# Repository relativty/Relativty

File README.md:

Dale una mirada a esta guía en [Español](README.es.md)
<h1 align="center">
	
</h1>

<h3 align="center">
	Open-source VR headset with SteamVR support.
</h3>
<p align="center">
	<strong>
		<a href="https://relativty.com">Website</a>
		•
		<a href="https://discord.gg/jARCsVb">Discord</a>
	</strong>
</p>

I’m <a href="https://twitter.com/maxim_xyz?lang=en">Maxim xyz</a> and when my best friend Gabriel Combe and I were 15 years old we built our own VR headset because we couldn't afford to buy one.

5 years later : this headset became Relativty.

* Fully Open-source - **hardware**, **software**, **firmware**.
* **Steam VR** support.
* Natively displays **2K** resolution at **120FPS**.
* Compatible with **Arduino**.
* Experimental **Body-Tracking**

**This repo serves as a Build guide, to learn more about the headset see you at <a href="https://relativty.com">Relativty.com</a>**

Made for Hackers
-
Relativty is **NOT A CONSUMER PRODUCT**. We made Relativty in my bedroom with a soldering iron and a 3D printer and we expect you to do the same: **build it yourself**.

Relativty at its basics is a 3 Degrees of Freedom (3-DoF) VR headset with no built-in controller support, designed to work with SteamVR.
This may limit its practical usability for games that demand knuckle-style VR controllers.
If you are looking for a more full-featured DIY VR project 6-Dof tracking and controller support, we recommend you check out <a href="https://github.com/HadesVR/HadesVR">HadesVR</a>.

Whether or not you are building either Relativty or HadesVR, or if you just want to join our community and hang out, we invite you to <a href="https://discord.gg/F8GNKjy6RF">Relativty's Guild on Discord</a>.

It is a place for the DIY/Open-Source VR community to learn, grow, share knowledge, and ask for help. 

# Start Building Relativty

# Building The Hardware
## 1. CURRENT RECOMMENDED BUILD - As of May 2023
### 1.1 Introduction
This is an updated build guide to help people who recently discovered Relativty. It aims to explain how to build the minimum functional product, which can be further improved upon and modified to the individual's liking. The original build guide can still be found further below.

            Following this guide to build a Relativty headset assumes basic understanding of electronics and programming Arduino boards.
            A VR headset is a complex system and can be difficult to figure out what is not working if you get stuck with the build.
            If you encounter any issues, join our Discord and ask for help, we are happy to assist.

### 1.2 ELECTRONICS

The following electronic components are required:

- ATmega32U4 Microcontroller (MCU) with USB HID support, such as an <a href="https://www.amazon.co.uk/diymore-Atmega32U4-Development-Microcontroller-Header/dp/B0BKGSVX2X">Arduino Pro Micro</a>
- Inertial Measurement Unit (IMU) that is supported by the <a href="https://github.com/LiquidCGS/FastIMU">FastIMU Library</a>
- A small, high resolution and high refresh rate PC display + driver board. <a href="https://github.com/HadesVR/HadesVR/blob/main/docs/Headset.md#displays">This segment of the HadesVR documentation presents possible good options you can choose from</a>. It is important to note that these displays connect to a DRIVER BOARD, which then connects to your computer. ALWAYS purchase the driver board and display(s) in the same bundle if you can to ensure they are compatible with each other. If you have further questions about displays, join us at <a href="https://discord.gg/F8GNKjy6RF">Relativty's Guild on Discord</a>.
```
NOTES on VR DISPLAYS:
- The display does not connect to the Microcontroller, it only connects to the Computer running your VR Apps.
- Technically, any PC display/monitor can be configured as the display used by Relativty. Therefore, you can simply test your build on your PC monitor
first to make sure it works, before you decide to spend a significant amount of money on lenses, display(s) and other parts.
- High performance, small form factor displays are expensive, and often very delicate. Handle them with care! :)
```

### 1.2.1 Wiring the IMU and MCU
The IMU needs to be connected to the MCU for power and communication.
The MCU connects to your computer via USB to send the IMU readings to SteamVR.

In case of an Arduino Pro Micro, you need to connect the following pins:
```
Pro Micro       IMU
VCC         ->  VCC  
GND         ->  GND  
SDA(pin 2)  ->  SDA  
SCL(pin 3)  ->  SCL  
```  
If you use a different MCU, the SDA and SCL pins might be mapped to different pin numbers.

Also, make sure that the VCC of your MCU is compatible with the rated operating voltage of your IMU.

Supplying incorrect voltage to electronic components may cause damage to them.

The MCU itself simply connects to your computer via the USB port.

### 1.2.2 Connecting the display
As mentioned previously, any display that is compatible with a personal computer should be able to function as your VR display.

In case you are using the recommended one or a similar component that is powered via micro-USB or other USB standard, it is possible that you will encounter situations where the board does not power up. This could be either because the micro-USB cable you are using is too long (so the board cannot power up because the voltage dropped too much), or the board is unable to turn on because the USB port it connects to on the computer side is simply unable to supply enough power. In this case, you might need to try different ports on your computer or a powered USB hub.

### 1.3 MECHANICAL BUILD

The following parts are required for the Mechanical Build:

- Housing - .STL files for 3D-printable model provided in Relativty_Mechanical_build folder.
- Lenses -  for building the 3D-printable headset, Lenses with 40mm diameter/50mm focal length required. You can often find these on Aliexpress or similar.
- Strap and Facial Interface - e.g. replacement strap + foam for HTC Vive. You can often find these on Aliexpress or similar.

If you do not have access to 3D-printing, it is also possible (and MUCH simpler) to just use an Android VR Phone case, and modify it to fit your screen and so that you can attach your IMU and MCU to it.

The advantage of this approach is that you get everything in one package, often including IPD adjustment.

### 1.4 SOFTWARE SETUP

### 1.4.1 Introduction

Relativty depends on 2 main software components:
- the Arduino firmware
- the SteamVR driver

As the system is designed to work with SteamVR, you need to have Steam installed and SteamVR downloaded on your computer.

### 1.4.2 Programming your MCU

As previously mentioned, we recommend you use an Arduino Pro Micro and an IMU supported by the FastIMU Library.
FastIMU is an awesome package that supports many commonly used IMUs and comes with a pre-written Arduino sketch that works with Relativty.

First, you will need to install the Arduino IDE and connect your MCU to your computer via the USB connector.

Once you have it connected and verified your Arduino IDE can work with your MCU, download FastIMU from the library manager.

Wire up your IMU as recommended in Section 1.2.1.

Find the Examples/Fastimu/Calibrated_relativty sketch in your Arduino IDE:

And finally, Upload it to your MCU.

FastIMU also includes a built-in calibration tool that can store the calibration data on the IMUs EEPROM.

Calibrating the IMU may help with sensor drift that you can experience over time while using Relativty.

After uploading Calibrated_relativty sketch to the IMU, you can open the Arduino Serial Monitor to initiate a calibration sequence:

      NOTE: you only have to do this once, but make sure to follow the instructions given to you in the serial monitor.

### 1.4.3 Installing The SteamVR Driver

To install the Relativty SteamVR driver:
- download the <a href="https://github.com/relativty/Relativty/archive/refs/heads/master.zip">master repository</a>
- inside Relativty-master find the Relativty_Driver\Relativty folder and copy it to your SteamVR installation's drivers directory.

### 1.4.4 Configuring The SteamVR Driver

Once you copied the driver files, it is time to configure the driver to work with your setup and computer.

Inside drivers\Relativty\resources\settings, there should be a file called default.vrsettings.

This is the configuration file for the driver.

There are a few things that you need to change.

### Configuring the driver to talk to the MCU
ASSUMING you use an Arduino Pro Micro and the FastIMU library:

In the Relativty_hmd segment find these values:
- hmdPid
- hmdVid
- hmdIMUdmpPackets

and change the values like so:

```
      "hmdPid" : 32823,
      "hmdVid": 9025,
      "hmdIMUdmpPackets":  false,
```

If you are using a different MCU, you need to figure out the USB PID and VID values.

Easiest way is to connect it to your computer via USB and check in Arduino IDE.

In the menu bar, select Tools/Get Board Info:

Take the PID and VID values and convert them to decimal with a <a href="https://www.rapidtables.com/convert/number/hex-to-decimal.html">hex converter</a>.

The converted values then go into the hmdPid and hmdVid values in default.vrsettings.

### Configuring the Display Settings
Now let's look at configuring the driver to work with your Display.

The config variables for the display are in the Relativty_extendedDisplay segment:

For the VR Viewport window's point of origin:
```
      "windowX" : 3440,
      "windowY" : 0,
```

For the VR Viewport's actual size
```
      "windowWidth" : 1920,
      "windowHeight" : 1080,
```

For the VR Viewport's rendering resolution - this should be normally the same as the size
```
      "renderWidth" : 1920,
      "renderHeight" : 1080,
```

And some miscellaneous settings:
```
      "DistortionK1" : 0.4,
      "DistortionK2" : 0.5,
      "ZoomWidth" : 1,
      "ZoomHeight" : 1,
      "EyeGapOffsetPx" : 0,
      "IsDisplayRealDisplay" : true,
      "IsDisplayOnDesktop" : true
```
If the point of origin and size is not configured correctly, the driver will crash and SteamVR will not display anything!

Therefore we need to have a look at and understand the coordinate system SteamVR uses for displays.

Windows always assumes one of the connected displays as your Primary Display.

You can verify which one is your Primary in Display Settings.

You can select each of your displays with the mouse. The one that has "Make this my main display" checkbox greyed out is your Primary Display.

THIS GUIDE ASSUMES THAT THE TOP EDGE OF ALL OF YOUR DISPLAYS ARE ALIGNED IN WINDOWS DISPLAY SETTINGS (as seen on the screenshots)

Consequently, checking the same on another, non-primary display will make that one your Primary.

The TOP LEFT corner of your Primary Display is the ORIGIN POINT of SteamVR's display coordinate system.

To be able to tell SteamVR where to draw the VR Viewport on your displays, you need to make sure you understand this fact and as a result can identify the correct point of origin for the Viewport.

For example, in a setup like this:

Because the "1" screen is the primary, and the "3" screen is the VR Display, the origin point (the 0,0 coordinate) is on the top left of the "1" screen.

This screen has 3440x1440 resolution.

This means it occupies the X axis from 0 to 3439, and the next screen on its right starts at point 3440.

Therefore, in this case the correct windowX and windowY values are:

```
      "windowX" : 3440,
      "windowY" : 0,
```

If "2" screen was the VR display (and "1" is still the Primary), the correct values would be:

```
      "windowX" : -1920,
      "windowY" : 0,
```
Because the "2" screen's coordinates occupy space over the other side of the origin point.

For windowWidth,windowHeight,renderWidth,renderHeight, simply set the Native Resolution of your VR display.

Once this is all set, save the settings file.

Now you should be ready to start SteamVR.

If everything is set up right, you should get straight into the vr holodeck area:

If you are encountering any issues with your build:
- open the SteamVR Web Console and copy the entire log file
- Join <a href="https://discord.gg/F8GNKjy6RF">Relativty's Guild on Discord</a>, tell us about the issues you are facing, and upload the log file in the chat. 

### IF YOUR VR WINDOW DISAPPEARS AFTER CLICKING ON IT:

Open Windows PowerShell and paste these commands into the command line, then hit enter:

```
get-process vrcompositor | stop-process -Force;cd "C:\Program Files (x86)\Steam\steamapps\common\SteamVR\bin\win64";.\vrcompositor.exe
```

Afterwards the VRCompositor should remain stable, so you only have to do this once per session.

# 2. LEGACY BUILD
The hardware is based on the Relativty Motherboard which includes an Atmel SAM3X8E ARM Cortex-M3 processor and uses an MPU-6050 as it’s IMU.
Alternatively, any processor that supports the ArduinoCore and is connected to an MPU-6050/MPU-9250 can be used as the hardware for Relativty. Both methods are explained below.

## Building The Relativty Motherboard
### PCB Manufacturing.

We first start with the naked PCB.

it can be manufactured and bought for around $4 on websites like <a href="https://jlcpcb.com/">jlcpcb</a>.

You’ll need to provide the Gerber file folder `Relativty_Electronics_build/GerberFiles.zip` which describes the shape of the board.

### Assembling

Soldering the components onto the naked PCB. 

You’ll have to buy the components listed in one of the two BOMs, depending on availability:
- `Relativty_Electronics_build/Assembly/jlcpcb.com_motherboard_BOM.csv` 
- `Relativty_Electronics_build/Assembly/motherboard_BOM.xlsx`

Where to position those components on the PCB is described in the file `Relativty_Electronics_source/motherboard.brd` which can be opened in Eagle.

#### Using an Arduino

An alternative to the Relativty Motherboard is to use an Arduino Due and to connect it to an MPU-6050.
```
5V      -> VCC  
GND     -> GND  
SDA(20) -> SDA  
SCL(21) -> SCL  
PIN 2   -> INT  
```

If you are using an MPU-9250 with the alternative firmware provided the pinout is:

```
5V      -> VCC  
GND     -> GND  
SDA(20) -> SDA  
SCL(21) -> SCL   
```

Then push the `ERASE` and the `RESET` button on the Arduino Due and you’ll be able to install the Relativty Firmware.

#### Installing The Relativty Firmware

You’ll now need to install the Relativty board in the Arduino IDE. 

To do that copy that JSON URL: https://raw.githubusercontent.com/relativty/Relativty/master/Relativty_Firmware/package_Relativty_board_index.json and open the Arduino IDE

In Arduino, Click File and then Preferences:

- If you are using the Relativty PCB, aad the JSON URL to the `Additional Boards Manager` text box.
- Go to `Tools > Board > Board Manager` and you should see the Relativty Board, click install.
- Reboot the Arduino IDE and under Tools > Boards, select Relativty.
- You can now open `Relativty_Firmware/firmware/firmware.ino` and upload it to your board.

If you are using a different board e.g. Arduino Due:

- install contents of `Relativty_Firmware\Relativty_board\` to your Arduino IDE
- if you are using MPU-6050, use `Relativty_Firmware/firmware/firmware.ino`
- if you are using MPU-9250, use `Relativty_Firmware\MP9250-HID\MP9250-HID\MP9250-HID.ino`

# Building The Mechanical Parts

## Assembling the HMD

All the files needed for the 3D printing can be found in the `Relativty_Mechanical_build` folder and the screws needed to assemble the Headset are listed in `screws_BOM.xlsx`.

We've used parts from Aliexpress:

- <a href="https://www.aliexpress.com/item/33058848848.html">The Strap</a>, 
- <a href="https://www.aliexpress.com/item/4000199486058.html">The Foam</a>,
- <a href="https://www.aliexpress.com/item/33029909783.html">The Lenses</a> (40mm diameter/50mm focal length).

### The screen for the HMD

Relativty Headset runs a dual-screen at 120FPS 2K, however, because of the open nature of Relativty you can equip it with any screen.

Our model can be found on Aliexpress, but depending on the vendor similar screens can cost from $150 to $190. You'll have to hunt and maybe wait for the right vendor at the right price to get the display for cheap (or buy in bulk). 

This is [the model we used](https://www.aliexpress.com/item/32975198897.html).

### Setting Up the Software

#### Installing Relativty Driver for SteamVR

The Relativty Driver is contained within `Relativty_Driver/Relativty` folder. 

⚠️ You’ll need to set it up by editing the JSON file `Relativty_Driver/Relativty/resources/settings/default.vrsettings`

If you are not using a Relativty PCB, you will need to change these:

      "hmdPid" : 9,
      "hmdVid": 4617,
	  
These are the USB HID device's unique Vendor and Producit Identifieres (pid/vid)

If you are using and Arduino Due, the correct values will be:

      "hmdPid" : 62,
      "hmdVid" : 9025,
	  
In case you are using a different board, the process to get the right values is as below:

1.	Plug your board in

2.	Select your board in Arduino IDE and click Tools/Get Board info. you will see something like this:

```
	BN: Arduino Due (Native USB Port)
	VID: 2341
	PID: 003e
	SN: HIDHB
```
3.	Make note of the VID and PID numbers. These are hexadecimal values.

	To apply them to the config, they need to be converted to int.
	
	If you are unsure how to do that, there is plenty online converters available.
	
	Such as: https://www.rapidtables.com/convert/number/hex-to-decimal.html

4.	Change your hmdPid and hmdVid values to the converted values.

Next, you need to set up the display coordinates and resolution.

At first, you should have the HMD's display set up as a secondary screen extending your desktop,

aligned onto the top right corner of your primary display.

In the config file's "Relativty_extendedDisplay" segment, find and set these:
```
      "windowX" : *whatever your primary screen resolution's width is*,
      "windowY" : 0,
      "windowWidth" : *HMD's native resolution width*,
      "windowHeight" : *HMD's native resolution height*,
      "renderWidth" : *HMD's native resolution width*,
      "renderHeight" : *HMD's native resolution height*,
	  
	  And at the bottom of this segment:
	  
      "IsDisplayRealDisplay" : true,
      "IsDisplayOnDesktop" : true
```  
	  
Make sure not to delete any "," symbols as that will break the config.

Only the last item in the config should not have a "," symbol.

If for whatever reason the above settings do not work out for you try:

Set your HMD display as a mirrored display of your primary display.

Change config as follows:
```
      "windowX" : 0,
      "windowY" : 0,
      "windowWidth" : *HMD's native resolution width*,
      "windowHeight" : *HMD's native resolution height*,
      "renderWidth" : *HMD's native resolution width*,
      "renderHeight" : *HMD's native resolution height*,
	
      "IsDisplayRealDisplay" : false,
      "IsDisplayOnDesktop" : true
	
```	
⚠️ Please note that this may result in keyboard/mouse input not being captured by the VR window, should your game require it, it might become unplayable.

You can also make IPD (Interpupillary Disance) adjustments within the configuration file:

In the "Relativty_hmd" segment find and adjust:

```
      "IPDmeters" : 0.063,
```

You can also change the lens distortion correction by changing these:

```
      "DistortionK1" : 0.4,
      "DistortionK2" : 0.5,
```

You can now install Relativty Driver:
- Locate your `vrpathreg.exe` program, usually located at `C:/Steam/steamapps/common/SteamVR/bin/win64/vrpathreg.exe`
- Then open the Windows Command Prompt and run the following commands:
`cd C:/Steam/steamapps/common/SteamVR/bin/win64
vrpathreg.exe`

And then assuming your `Relativty_Driver/Relativty` driver folder is located at:
`C:/code/Relativty_Driver/Relativty`
- run `vrpathreg adddriver C:/code/Relativty_Driver/Relativty`

Relativty Driver is now installed. You can uninstall it any time by running:  
- `vrpathreg removedriver C:/code/Relativty_Driver/Relativty`

#### Setting up the Experimental 3D Tracking

The tracking is still very experimental and can only be run on NVIDIA GPU due to the usage of CUDA. The tracking makes uses of only a video input and an Artificial Neural Network AI trained to estimate a 3D body position. 

This method is nothing close to the precision or freedom of movements of a dedicated sensor however we believe that the model can be trained and improved by orders of magnitude.

You first need to connect a webcam to your computer and install Python 3.8.4 and select the option to add it to the path. Then install `PyTorch`, you can do so by running the following commands:

`python -m pip install torch===1.6.0 torchvision===0.7.0 -f https://download.pytorch.org/whl/torch_stable.html`

Then proceed to install `CUDA Toolkit 11.0.`

You’ll then need to download the Folder `PYTHONPATH` at https://github.com/relativty/Relativty/releases and add its location to `PyPath` in the `JSON Relativty_Driver/Relativty/resources/settings/default.vrsettings`

Set `tracking` to 1. The tracking is now turned on and can be turned off anytime by setting `tracking` to 0. The tracking can also be calibrated depending on your camera, this can be done by tweeking `scalesCoordinateMeter` and `offsetCoordinate`. `scalesCoordinateMeter` correspond to the delta of coordinates in a given axis calculated by the AI after normalization when you move 1 meter in that given axis.

**Note:** If you plan on using mpu9250 firmware do not forget to switch to it in the driver by setting `hmdIMUdmpPackets` to `false`:
`"hmdIMUdmpPackets":  false,`

## Final Steps

Everything is now set up to start playing. 

To start using Relativty:
- Lay the headset on a flat surface with the front panel facing the ground
- Plug in the Headset.
It’ll automatically calibrate after a few seconds.

You can now run any SteamVR game!

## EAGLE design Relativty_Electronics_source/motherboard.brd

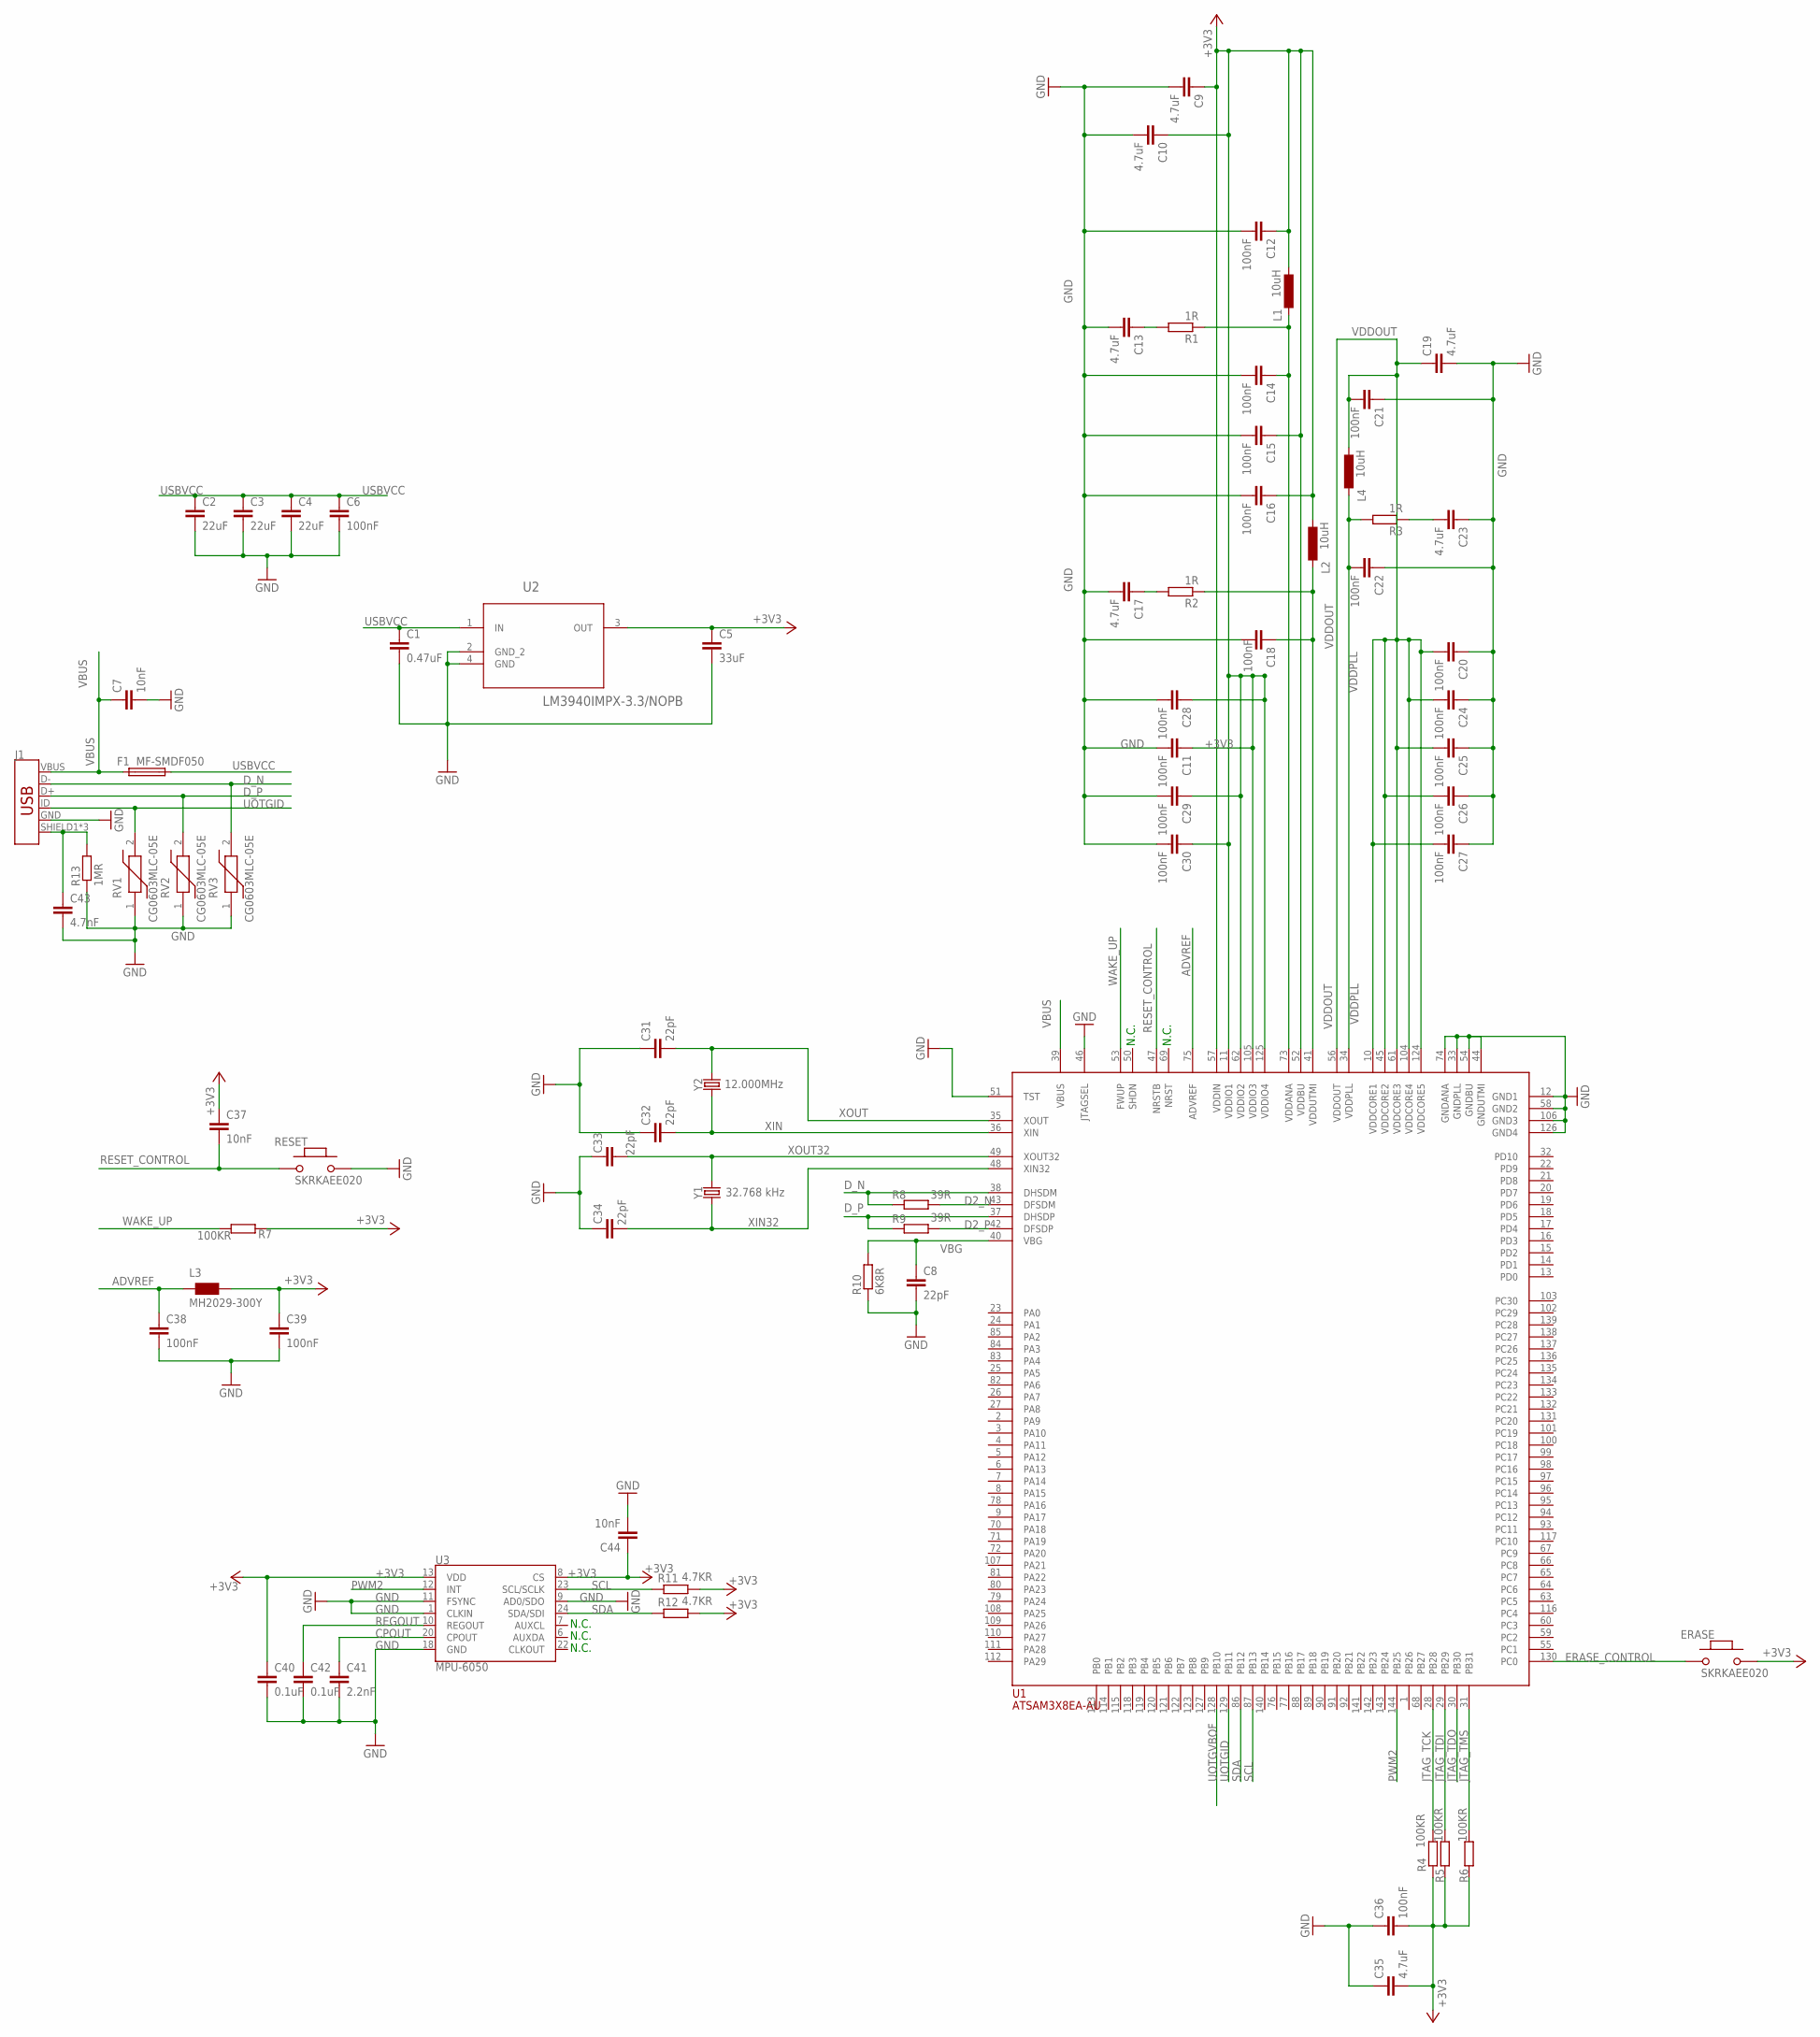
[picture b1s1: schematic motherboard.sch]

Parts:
C1: 0.47uF; C0805
C2, C3, C4: 22uF; C1206
C5: 33uF; C1206
C6, C11, C12, C14, C15, C16, C20, C21, C22, C24, C25, C26, C27, C28, C29, C30, C36, C38, C39: 100nF; C0402
C7, C37, C44: 10nF; C0402
C8, C31, C32, C33, C34: 22pF; C0402
C9, C10, C13, C17, C19, C23, C35: 4.7uF; C0805
C18: 100nF; C0201
C40, C42: 0.1uF; C0402
C41: 2.2nF; C0402
C43: 4.7nF; C0402
ERASE: SKRKAEE020; SOD4829X200
F1: MF-SMDF050
J1: USB_MICRO-B_FEMALE-SMT; USB-B-MICRO-SMD
L1, L2, L4: 10uH; L2012C
L3: MH2029-300Y; 2012-EU
R1, R2, R3: 1R; R0402
R4, R5, R6, R7: 100KR; R0603
R8, R9: 39R; R0402
R10: 6K8R; R2012
R11, R12: 4.7KR; R0805
R13: 1MR; R1206
RESET: SKRKAEE020; SOD4829X200
RV1, RV2, RV3: CG0603MLC-05E; VARC1608X55N
U1: ATSAM3X8EA-AU; LQFP144
U2: LM3940IMPX-3.3/NOPB; SOT230P696X180-4N
U3: MPU-6050; QFN-24-EP
Y1: 32.768 kHz; CRYSTAL-SMD-3.2X1.5MM
Y2: 12.000MHz; CRYSTAL-SMD-3.2X2.5MM

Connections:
+3V3: C5.1, C9.1, C10.1, C11.1, C12.1, C15.1, C16.1, C28.1, C29.1, C30.1, C35.2, C36.2, C37.1, C39.1, C40.1, C44.1, ERASE.2, L1.1, L2.1, L3.2, R4.1, R5.1, R6.1, R7.1, R11.2, R12.2, U1.11 (VDDIO1), U1.52 (VDDBU), U1.57 (VDDIN), U1.62 (VDDIO2), U1.105 (VDDIO3), U1.125 (VDDIO4), U2.3 (OUT), U3.8 (CS), U3.13 (VDD)
ADVREF: C38.1, L3.1, U1.75 (ADVREF)
CPOUT: C41.1, U3.20 (CPOUT)
D2_N: R8.2, U1.43 (DFSDM)
D2_P: R9.2, U1.42 (DFSDP)
D_N: J1.D-, R8.1, RV3.2, U1.38 (DHSDM)
D_P: J1.D+, R9.1, RV2.2, U1.37 (DHSDP)
ERASE_CONTROL: ERASE.1, U1.130 (PC0)
GND: C1.2, C2.2, C3.2, C4.2, C5.2, C6.2, C7.2, C8.2, C9.2, C10.2, C11.2, C12.2, C13.2, C14.2, C15.2, C16.2, C17.2, C18.2, C19.2, C20.1, C21.1, C22.1, C23.1, C24.1, C25.1, C26.1, C27.1, C28.2, C29.2, C30.2, C31.1, C32.1, C33.1, C34.1, C35.1, C36.1, C38.2, C39.2, C40.2, C41.2, C42.2, C43.2, C44.2, J1.GND, R10.1, R13.1, RESET.2, RV1.1, RV2.1, RV3.1, U1.12 (GND1), U1.33 (GNDPLL), U1.44 (GNDUTMI), U1.46 (JTAGSEL), U1.51 (TST), U1.54 (GNDBU), U1.58 (GND2), U1.74 (GNDANA), U1.106 (GND3), U1.126 (GND4), U2.2 (GND_2), U2.4 (GND), U3.1 (CLKIN), U3.9 (AD0/SDO), U3.11 (FSYNC), U3.18 (GND)
JTAG_TCK: R4.2, U1.28 (PB28)
JTAG_TDI: R5.2, U1.29 (PB29)
JTAG_TDO: U1.30 (PB30)
JTAG_TMS: R6.2, U1.31 (PB31)
unnamed: C43.1, J1.SHIELD1 (SHIELD), J1.SHIELD2 (SHIELD), J1.SHIELD3 (SHIELD), R13.2
unnamed: C13.1, R1.2
unnamed: C17.1, R2.2
unnamed: C23.2, R3.1
unnamed: C14.1, L1.2, R1.1, U1.73 (VDDANA)
unnamed: C18.1, L2.2, R2.1, U1.41 (VDDUTMI)
PWM2: U1.144 (PB25), U3.12 (INT)
REGOUT: C42.1, U3.10 (REGOUT)
RESET_CONTROL: C37.2, RESET.1, U1.47 (NRSTB)
SCL: R11.1, U1.87 (PB13), U3.23 (SCL/SCLK)
SDA: R12.1, U1.86 (PB12), U3.24 (SDA/SDI)
UOTGID: J1.ID, RV1.2, U1.129 (PB11)
UOTGVBOF: U1.128 (PB10)
USBVCC: C1.1, C2.1, C3.1, C4.1, C6.1, F1.2, U2.1 (IN)
VBG: C8.1, R10.2, U1.40 (VBG)
VBUS: C7.1, F1.1, J1.VBUS, U1.39 (VBUS)
VDDOUT: C19.1, C20.2, C21.2, C24.2, C25.2, C26.2, C27.2, L4.1, U1.10 (VDDCORE1), U1.45 (VDDCORE2), U1.56 (VDDOUT), U1.61 (VDDCORE3), U1.104 (VDDCORE4), U1.124 (VDDCORE5)
VDDPLL: C22.2, L4.2, R3.2, U1.34 (VDDPLL)
WAKE_UP: R7.2, U1.53 (FWUP)
XIN: C32.2, U1.36 (XIN), Y2.1
XIN32: C34.2, U1.48 (XIN32), Y1.P$1 (1)
XOUT: C31.2, U1.35 (XOUT), Y2.3 (2)
XOUT32: C33.2, U1.49 (XOUT32), Y1.P$2 (2)

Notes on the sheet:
N.C.

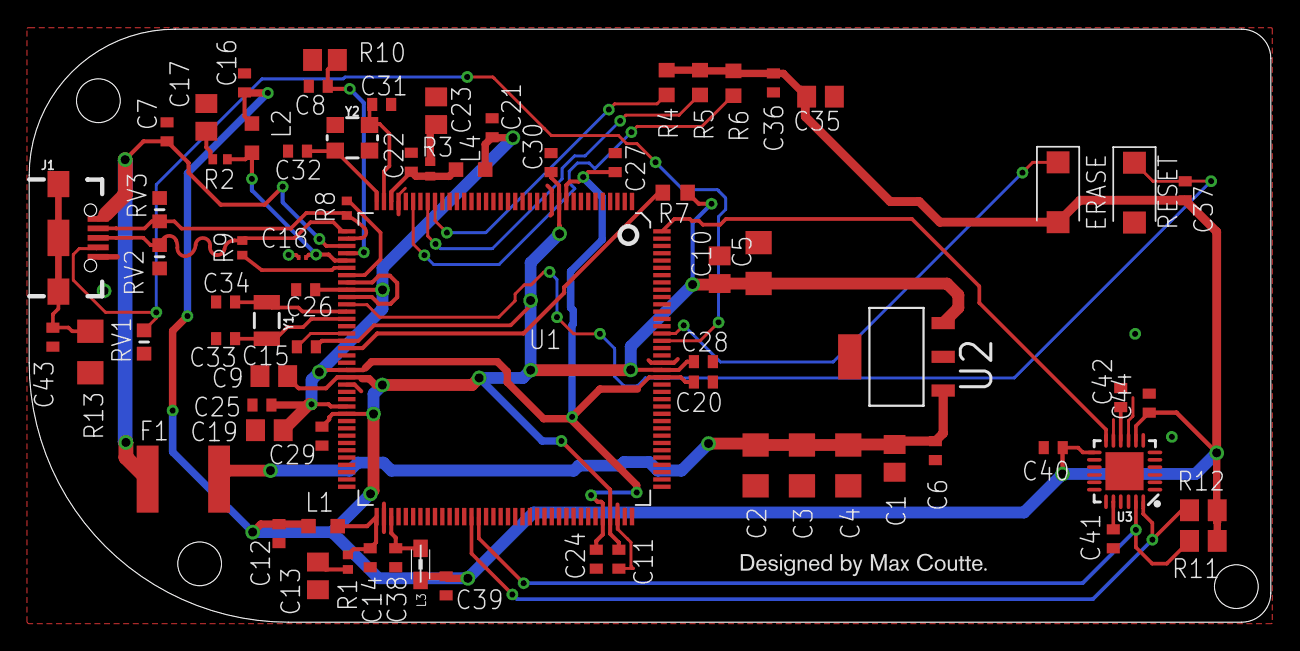
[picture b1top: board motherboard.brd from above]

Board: 2 copper layers, 85.1 x 40.6 mm, 73 parts (0 on the bottom side), 34 nets.

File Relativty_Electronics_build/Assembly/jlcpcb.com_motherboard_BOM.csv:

Comment,Designator,Footprint,LCSC Part #（optional）
USB_MICRO-B_FEMALE-SMT,J1,USB-B-MICRO-SMD,
0.1uF,"C40, C42",0402,C1525
0.47uF,C1,0805,C13967
100KOhm,"R4, R5, R6, R7",0603,C25803
100nF,C18,0402,C1525
100nF,"C6, C11, C12, C14, C15, C16, C20, C21, C22, C24, C25, C26, C27, C28, C29, C30, C36, C38, C39",0402,C1525
10nF,"C7, C37, C44",0402,C15195
10uH,"L1, L2, L4",0805C,C1046
12MHz,Y2,CRYSTAL-SMD-3.2X2.5MM,C93234
1MOhm,R13,1206,C17927
1Ohm,"R1, R2, R3",0402,C25125
2.2nF,C41,0402,C1531
22pF,"C8, C31, C32, C33, C34",0402,C1555
22uF,"C2, C3, C4",1206,C5672
32.768 kHz,Y1,CRYSTAL-SMD-3.2X1.5MM,C32346
33uF,C5,1206,C128347
39Ohm,"R8, R9",0402,C25110
4.7KOhm,"R11, R12",0805,C17673
4.7nF,C43,0402,C1538
4.7uF,"C9, C10, C13, C17, C19, C23, C35",0805,C1779
6.8KOhm,R10,0805,C17772
ATSAM3X8EA-AU,U1,LQFP144,C79305
CG0603MLC-05E,"RV1, RV2, RV3",0603,C20959
LM3940IMPX-3.3/NOPB,U2,SOT-223-4,C140319
MF-SMDF050,F1,MF-SMDF050,C12558
Beads,L3,0805,C1015
MPU-6050,U3,24-QFN (4x4),C24112
SKRKAEE020,"ERASE, RESET",SOD4829X200,

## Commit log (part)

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2017-12-03 Added 3D models
2017-12-03 spelling mistake
2017-12-04 Change wrong dimensions
2017-12-09 added strap holder
2017-12-09 added box_screen_adaptor
2017-12-27 added box_screen_spherecal
    Optional astetics update
2018-01-02 Added basics for Arduino Due
2018-01-02 added gitattributes
2018-01-04 Corrected some typos here and there
2018-01-04 little update readme
2018-01-04 Corrected some typo
2018-01-04 Added serial print for non-native USB controller
2018-01-04 Added Gif
2018-01-05 Correct and update
2018-01-15 Wrong Twitter link
2018-01-19 Fixed headset serial interuption
2018-01-21 Added a discord
2018-01-21 Update README.md
    Fixed one very minor typo.
2018-01-21 Use global urls for ali and ebay
2018-01-21 Fixed grammar
    Pretty sure that this is what you meant... how it was meant the exact opposite! :- )
2018-01-21 Fix typo in Atman's name
2018-01-23 📝 Fixed typo
2018-01-30 Fixed grammar
2018-02-08 Fix case sensitivity typo. A user was confused by this point. We are not making a static call to the function start(), but invoking it on the already existing instance of the Relativ class, named 're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
2018-03-09 wip: adding inertial tracking algorithm from LaValle text
2018-03-10 wip: added drift correction logic for test
2018-05-04 Added extra caution
2018-05-04 Added extra caution (#25)
2018-06-06 Added own 3D-Models for improved version of the headset Added notes.txt Added Schematic of the project
2018-06-15 wip: [Feature Request] inertial tracking using the onboard imu #21 (#23)
    * wip: adding inertial tracking algorithm from LaValle text
    * wip: added drift correction logic for test
    * wip: added drift correction logic for test
2018-06-18 Update README.md
    Seamlessly integrated last additions to the readme, added references where needed
2018-10-21 Bugfix main.ino
    error 'class VectorFloat' fixed by
2018-10-29 Added bug report issue templates
2018-10-29 Updatet Bug report issue template
2018-11-01 Revert "Bugfix main.ino (#28)"
    This reverts commit 511f065d39e91e90f41ba4807633f80bdecd8b8a.
2018-11-01 Revert "Bugfix main.ino (#28)" (#31)
    This reverts commit 511f065d39e91e90f41ba4807633f80bdecd8b8a.
2018-11-04 Revert "Bugfix main.ino (#28)" (#32)
    This reverts commit 511f065d39e91e90f41ba4807633f80bdecd8b8a.
2018-12-23 Update README.md (#35)
    Added Yxxy mention in Readme.md
2018-12-23 Corrected an Error in Readme
    anchor not set correctly
2018-12-23 Update README.md
    Added extra details for the Yxxy distro
2019-04-03 The yxxy distro (#38)
    * Update README.md
    * Added own 3D-Models for improved version of the headset
    Added notes.txt
    Added Schematic of the project
    * Update README.md
    * Update README.md
2019-04-12 Vang1 | 3D models
    Added the 3D models of Vang1, so people can choose between the models from Vang1, and TheYXXY.
2019-04-12 Changed folder name
    Changed the Folder name "3D models" to "TheYXXY 3D models"
2019-04-12 Changed reamde
    Added some changes for Vang1's 3D models.
2019-04-12 Added info about Vang1's 3D models
    Added more info about what you need to make the Vang1 3D models.
2019-04-12 Add 2 issue templates.
    Add 2 standard issue templates, to make it more easy for other people.
    * Added Bug report template
    * Added Future request template
2019-04-14 Create CODE_OF_CONDUCT.md (#40)
2019-04-14 Add 2 issue templates. (#41)
    Add 2 standard issue templates, to make it more easy for other people.
    * Added Bug report template
    * Added Future request template
2019-04-17 added STM32 code
    Added STM32 code
    Moved some files to different folders, to make the GitHub more userfriendly.
2019-04-17 Removed a file
    Removed a file, becuase the info has been added to the main README.md
2019-04-17 Fixed link
    Fixed the link for the face foam.
2019-04-17 Fixed typo
    Fixed a typo of the Biconvex lenses
2019-04-17 Fixed typo's
    Fixed a few more typo's in the Readme.MD
2019-04-17 Added a CONTRIBUTING.MD
2019-04-18 Added info Vang1 design
    Added the amount of screws needed to make the Vang1 VR headset.
2019-04-18 Added images
    Added extra images, to help people build the headset.
2019-04-22 Added STM32 code, and fixes in Readme.MD (#43)
    * added STM32 code
    Added STM32 code
    Moved some files to different folders, to make the GitHub more userfriendly.
    * Removed a file
    Removed a file, becuase the info has been added to the main README.md
    * Update README.md
2019-05-24 Added electronic 3D models
    Added the 3D models of the electronics, made by BioToa7 / Assemdox
2019-05-27 Added hardware 3D models
    Added the hardware 3D models, made by Bio Toa7 / Assemdox
2019-05-31 Fix 3D Models
    YXXY Model
    Part1 intersecting triangles
    Part2a overlapping triangles
    Part 2c intersecting triangles and overlapping triangles
    Part 2d overlapping triangles
    Vang1 Model
2019-06-24 Moving 3D models to thingiverse
    Due to the amount of new 3D models, and remixes that are made of them, we have decided to move our 3D models to thingiverse, and can all be found here; https://www.thingiverse.com/Relativty/designs t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
2020-09-09 fresh-start
2020-09-09 Create LICENSE
2020-09-09 new hardware, software and firmware
    Much lower latency, full SteamVR supports, 2K@120FPS Display, and much more.
2020-09-09 gitattributes
2020-09-09 readme-testing
2020-09-10 title.png
    Title for readme
2020-09-10 Improved Clarity of Readme (#55)
    * Update README.md
    * title.png
    Title for readme
    * Update README.md
    * Delete Title.png
    * title.png
2020-09-10 Fixed conflict error
2020-09-10 Removed Conflict Errors
    Removed Conflict Errors & Improved Clarity
2020-09-10 Remove duplicate paragraph from readme
2020-09-11 Added Discord Server Link
2020-09-13 gitignore cleanup
2020-09-13 idk, still trying to fix hid linking errors
2020-09-13 i hate VS
2020-09-13 ahhhhhhhhhhhhhhhhhhhh
2020-09-13 back to unresolved external symbol errors uh........
2020-09-13 x86 compiles
2020-09-13 x86 driver compiled
2020-09-13 forgot to change this
2020-09-13 missing dlls for driver, by @7ep3s#2748
2020-09-13 pid vid are now set by the config
2020-09-13 now logs device vid pid on fail
2020-09-13 forgot to add libs back after gitignore purge
2020-09-14 new standalone extended display component
    hmd device is not move to using it yet
2020-09-14 stuff
2020-09-14 hmd device moved to using standalone display component
2020-09-14 hmd render model
2020-09-14 proper render models
2020-09-14 better errors
2020-09-14 compiled
2020-09-14 driver log, had to be a static lib bc VS is bs
2020-09-15 "compile instructions"
2020-09-15 minor changes
2020-09-15 Add Lens specifications so correct lenses can be procured.
2020-09-15 hmd bindings
    yes hmds need to have them too
2020-09-15 new config and comments
2020-09-15 small change
2020-09-15 m_Pose.result fix
2020-09-16 comments
2020-09-16 compile
2020-09-16 comment
2020-09-20 added mpu9250 support
2020-09-20 uploaded wrong firmware previously
2020-09-20 changed default.vrsettings pid/vid and resolution values to match original defaults
2020-09-20 more settings for extended display component
    also updated openvr_driver.h
2020-09-23 allot of changes
    * few config sections renamed
    * added ipd setting
    * hmd imu type string setting changed to hmd imu dmp packets bool
    * when hid comm is in quat mode, packet and pose quats are mapped 1 to 1
    * minor pose update thread change
    * driver now logs its "version"
2020-09-23 forgot to change this back
2020-09-24 quat output reorder
2020-09-26 opt fix, still need to compile it
2020-10-11 enabled undistort, recompiled dlls
2020-11-17 Note on mpu9250
    Reminder to set hmdIMUdmpPackets to false in the driver for mpu9250 usage.
    Courtesy of @okawo80085
2021-01-14 lowered clock to make it compatible with micro and leonardo
2021-01-14 lowered clock
2021-01-25 Fixed "iteration 3 invokes undefined behavior"
2021-01-25 Changed c-arrays of atomics to std::arrays
2021-02-03 Changed `quat` in struct `pak` to a `float[4]`
2021-10-12 Add description and list of possible displays
2021-10-12 Add more listings
2022-01-20 README: Fix wrong terminology
    By using "Open-source" you are implying that this design is not complying with GPLv3 meaning that it restricts the right to use, study, improve and share.
    This replaces the wrong terminology with the terminology used by Free Software Foundation ("FSF").
    NOTE: FSF is not using the term `Technoliberal` (https://en.wikipedia.org/wiki/Technoliberalism), it's used in the EU politics to clarify that "Free Software" is not "Socialist Software" as people ge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
    NOTE: FSF uses the term `Free Hardware Designs` instead of `Free Hardware` to make the term more understandable by the public [http
2022-01-20 `Free and Open-source` instead of technoliberal
2022-01-21 README: Clarify lens type
    The aliexpress listing lists (assumed) "negative menuscus" lenses as "fresnel lenses", this is to avoid confusion.
    Difference in lens types:
    https://en.wikipedia.org/wiki/Lens#Types_of_simple_lenses
2022-02-18 Translated README.md into Japanese.
2022-02-18 Rename README.md to README-ja.md
2022-11-13 linux support (UNTESTED)
2022-11-13 fixed serial and linux build
2022-11-13 updated readme and changed the default config to the same old defaults
2022-11-18 Commit before breaking everyting
2022-11-18 Made the whole project into a cmake project so to avoid issue with submodules.
    I added dependencies that once were directly copied into the project as
    git submodules.
    The serial driver works on windows but you need to lower the baudrate if
    you wan a good experience (and you might have to set the baud rate in
    windows' device manager).
2022-11-18 Clean exit for serial. linux is still unreliable at startup. fixed linux compilation
2022-11-20 Made serial more reliable
    changed the default bitrate to a lower one.
    high bitrate cause issues with counterfited arduinos
    i still recommend increasing the baudrate as hight as your arduino can do
    add parity verification. this should erase a few errors.
    added reconnection on connection loss.
2022-11-20 Removed cmake logs
2022-11-20 Fixed linux serial and broke windows serial.
    i removed lib serial port since it was preventing us from fixing the linux serial input.
2022-11-20 Changed the serial interface to be object-oriented
    this change mask the differences between windows and linux.
2022-11-21 Updated the windows dll
2022-11-21 Updated the readme
2022-11-22 Removed outdated README(relativty_driver/) and add git instructions
    - fixed the .gitmodule config
2022-12-01 Add mingw support
    This is not meant to build windows binaries. but to be able to test if a windows build is possible from linux.
    this should reduce the number of reboot required to check if it work on both linux and windows
2022-12-07 Removed precompiled windows binary from the repository
2022-12-07 clean the code
2022-12-07 preliminary work for joycon and camera based tracking
2023-05-21 updating readme with new build guide
2023-05-21 more screenshots
2023-05-21 moar updates
2023-05-23 more screenshots + pid vid setup
2023-05-23 screenshots + pid vid setup guide
2023-05-23 fixed typo
2023-05-24 changed display guidance text + updated url
2023-05-28 I forgot what i did back then. but it seems to be mostly code cleanup and prepwork for making my own controller driver.
2023-07-08 fixed windows compile errors
2023-07-08 added some forgotten lines to HMDDriver::Activate
2023-07-08 removed old commented out HMDDriver::Activate to clean up a bit
2023-07-08 cleanup
2023-07-08 added 6dof pose server
2023-08-02 Update Relativty_HMDDriver.cpp
    fixed typo in pose server case
2023-08-02 Update default.vrsettings
    changed default selectedTracker to hid (0)
    0=hid
    1=serial
    2=poseserver
2023-10-21 Add FOV setting
2023-11-21 Update README.md
    added workaround for vanishing vrcompositor issue
2024-01-13 typo
2024-03-28 Readme espanish edition
2024-03-28 Adding link to navigate back and forth between readmes

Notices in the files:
parts and their libraries:
SparkFun-Connectors: Licensing: Creative Commons ShareAlike 4.0 International - https://creativecommons.org/licenses/by-sa/4.0
